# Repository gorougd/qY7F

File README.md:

### MPU based on STM32MP157

* Hardware design: 100Mbps Ethernet (TO BE FIXED)
* 512MB / 4Gbit DDR3L single bank (routed on PCB)
* 40pin RGB Screen adapter
* No PMU, discrete DC-DC power

By Gorougd, ZxS at Spring / Early Summer 2024

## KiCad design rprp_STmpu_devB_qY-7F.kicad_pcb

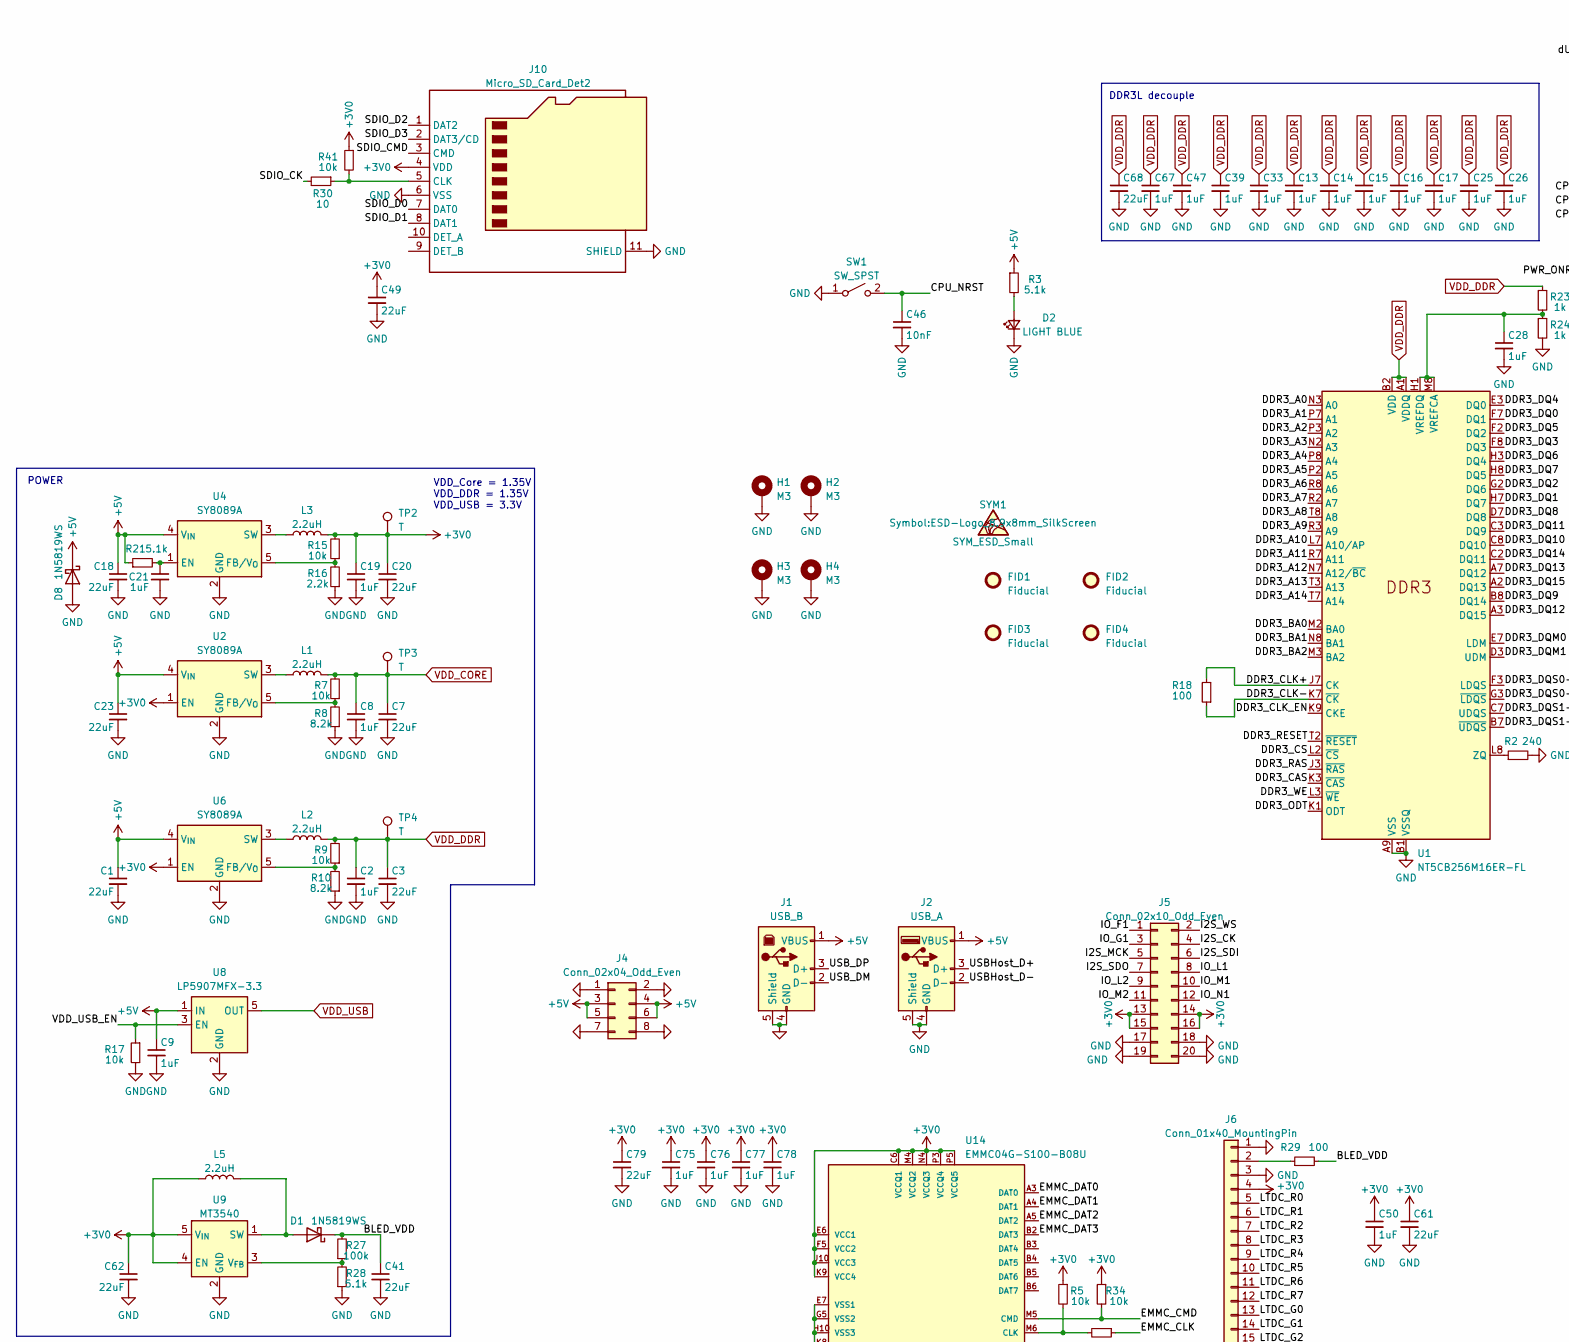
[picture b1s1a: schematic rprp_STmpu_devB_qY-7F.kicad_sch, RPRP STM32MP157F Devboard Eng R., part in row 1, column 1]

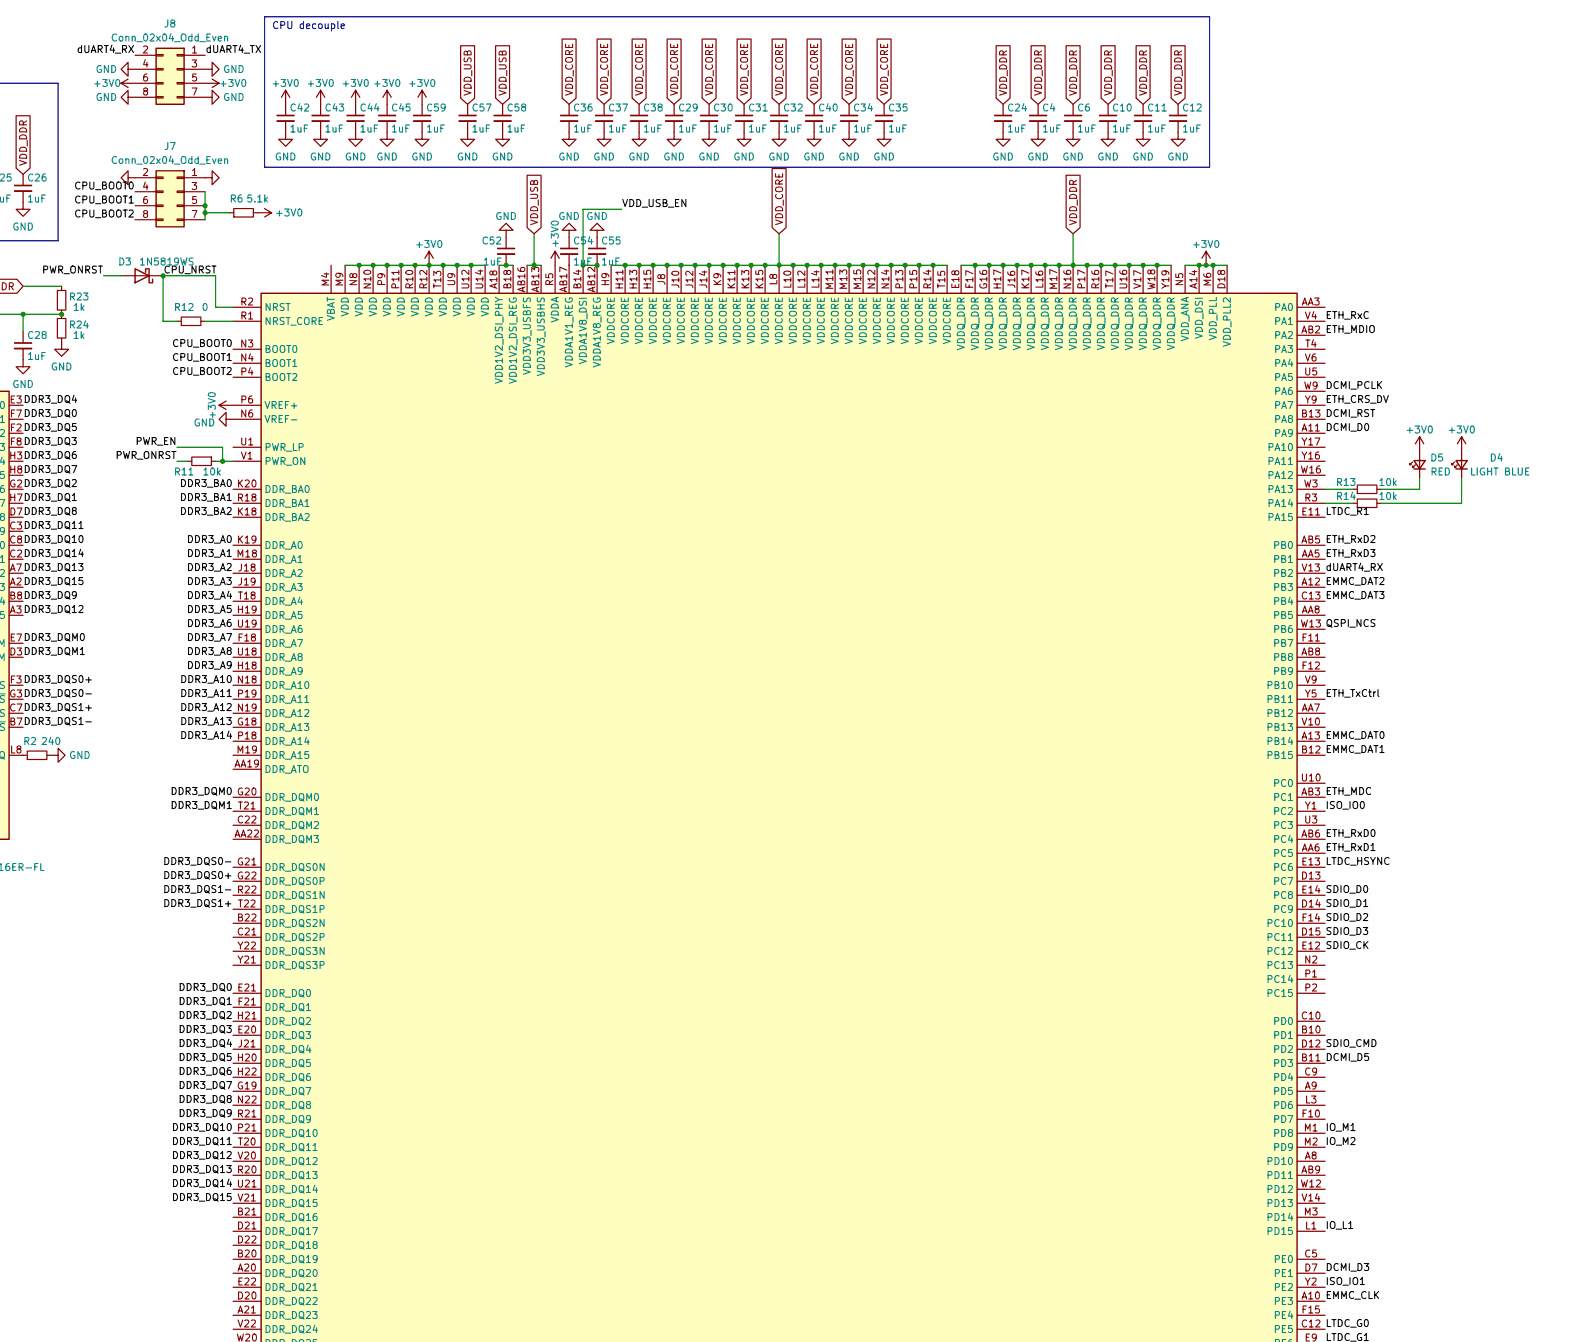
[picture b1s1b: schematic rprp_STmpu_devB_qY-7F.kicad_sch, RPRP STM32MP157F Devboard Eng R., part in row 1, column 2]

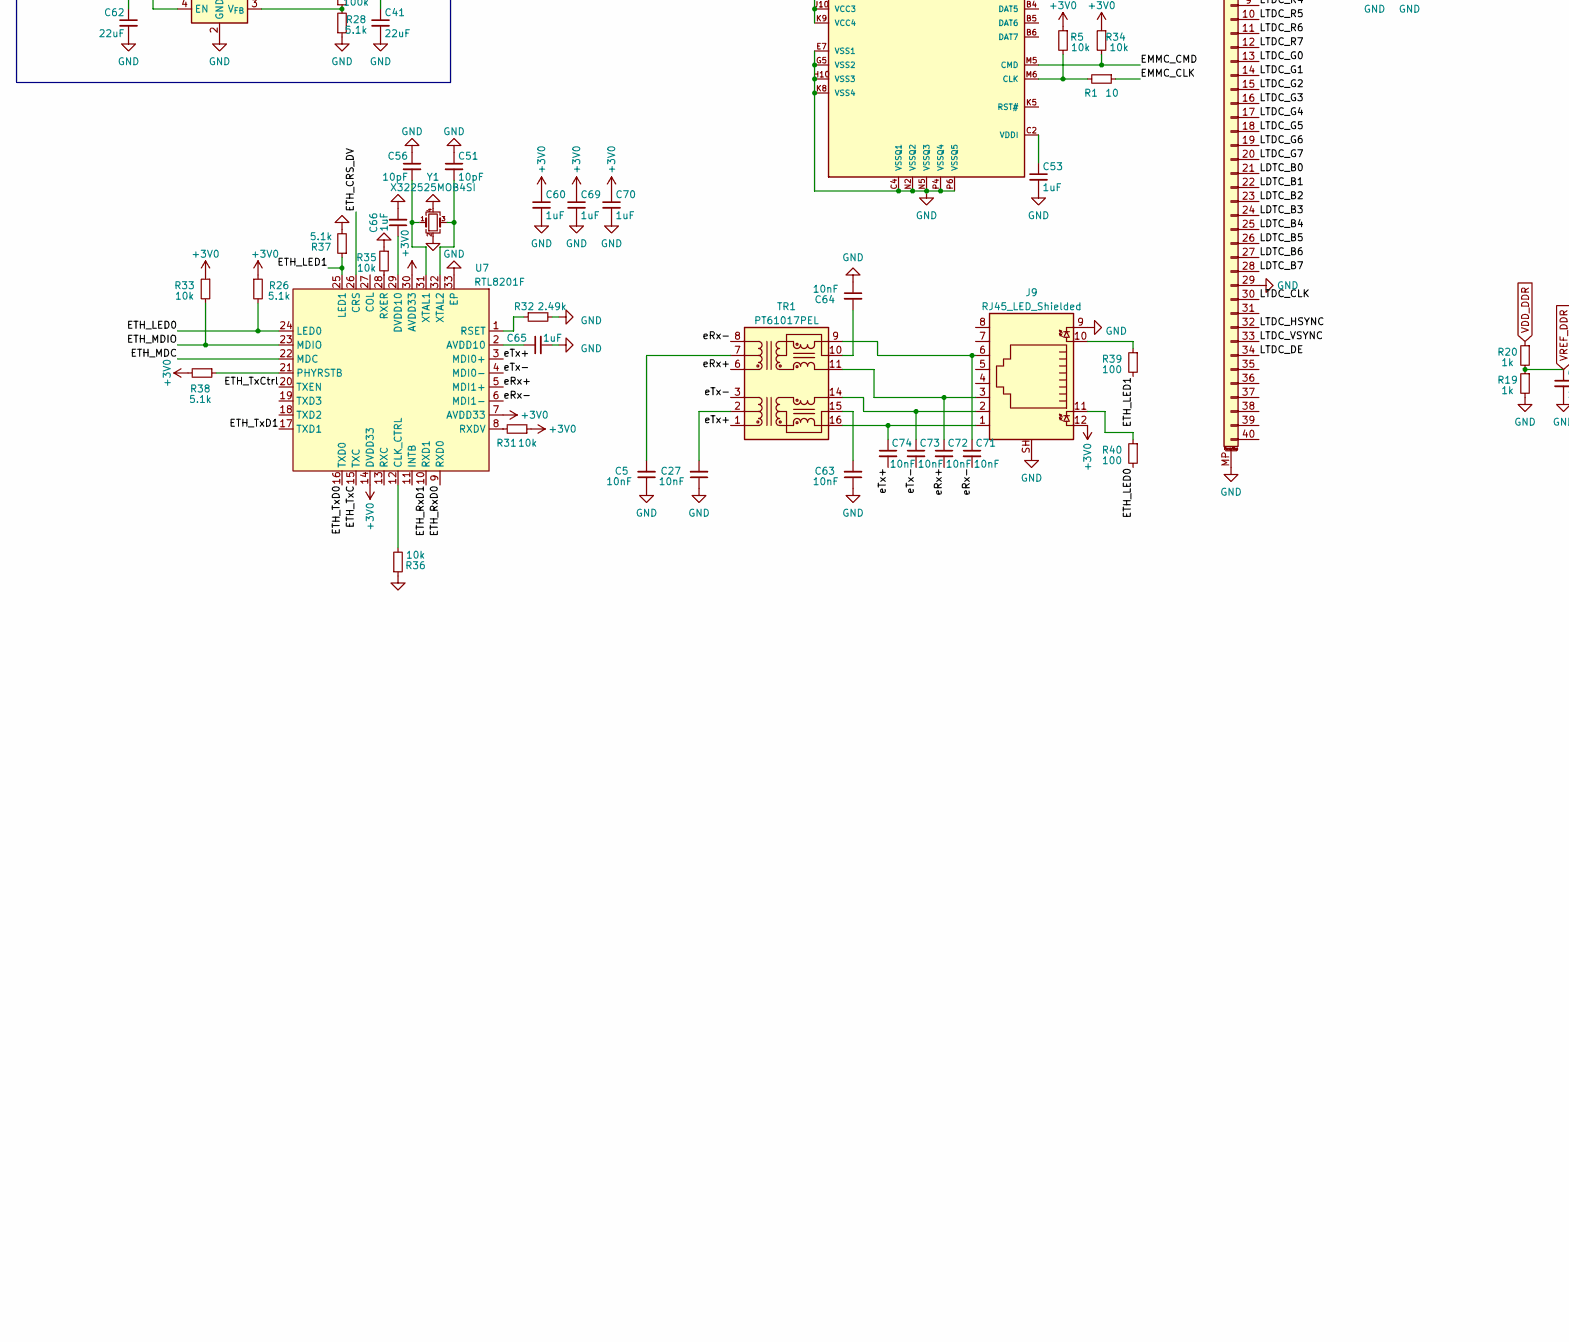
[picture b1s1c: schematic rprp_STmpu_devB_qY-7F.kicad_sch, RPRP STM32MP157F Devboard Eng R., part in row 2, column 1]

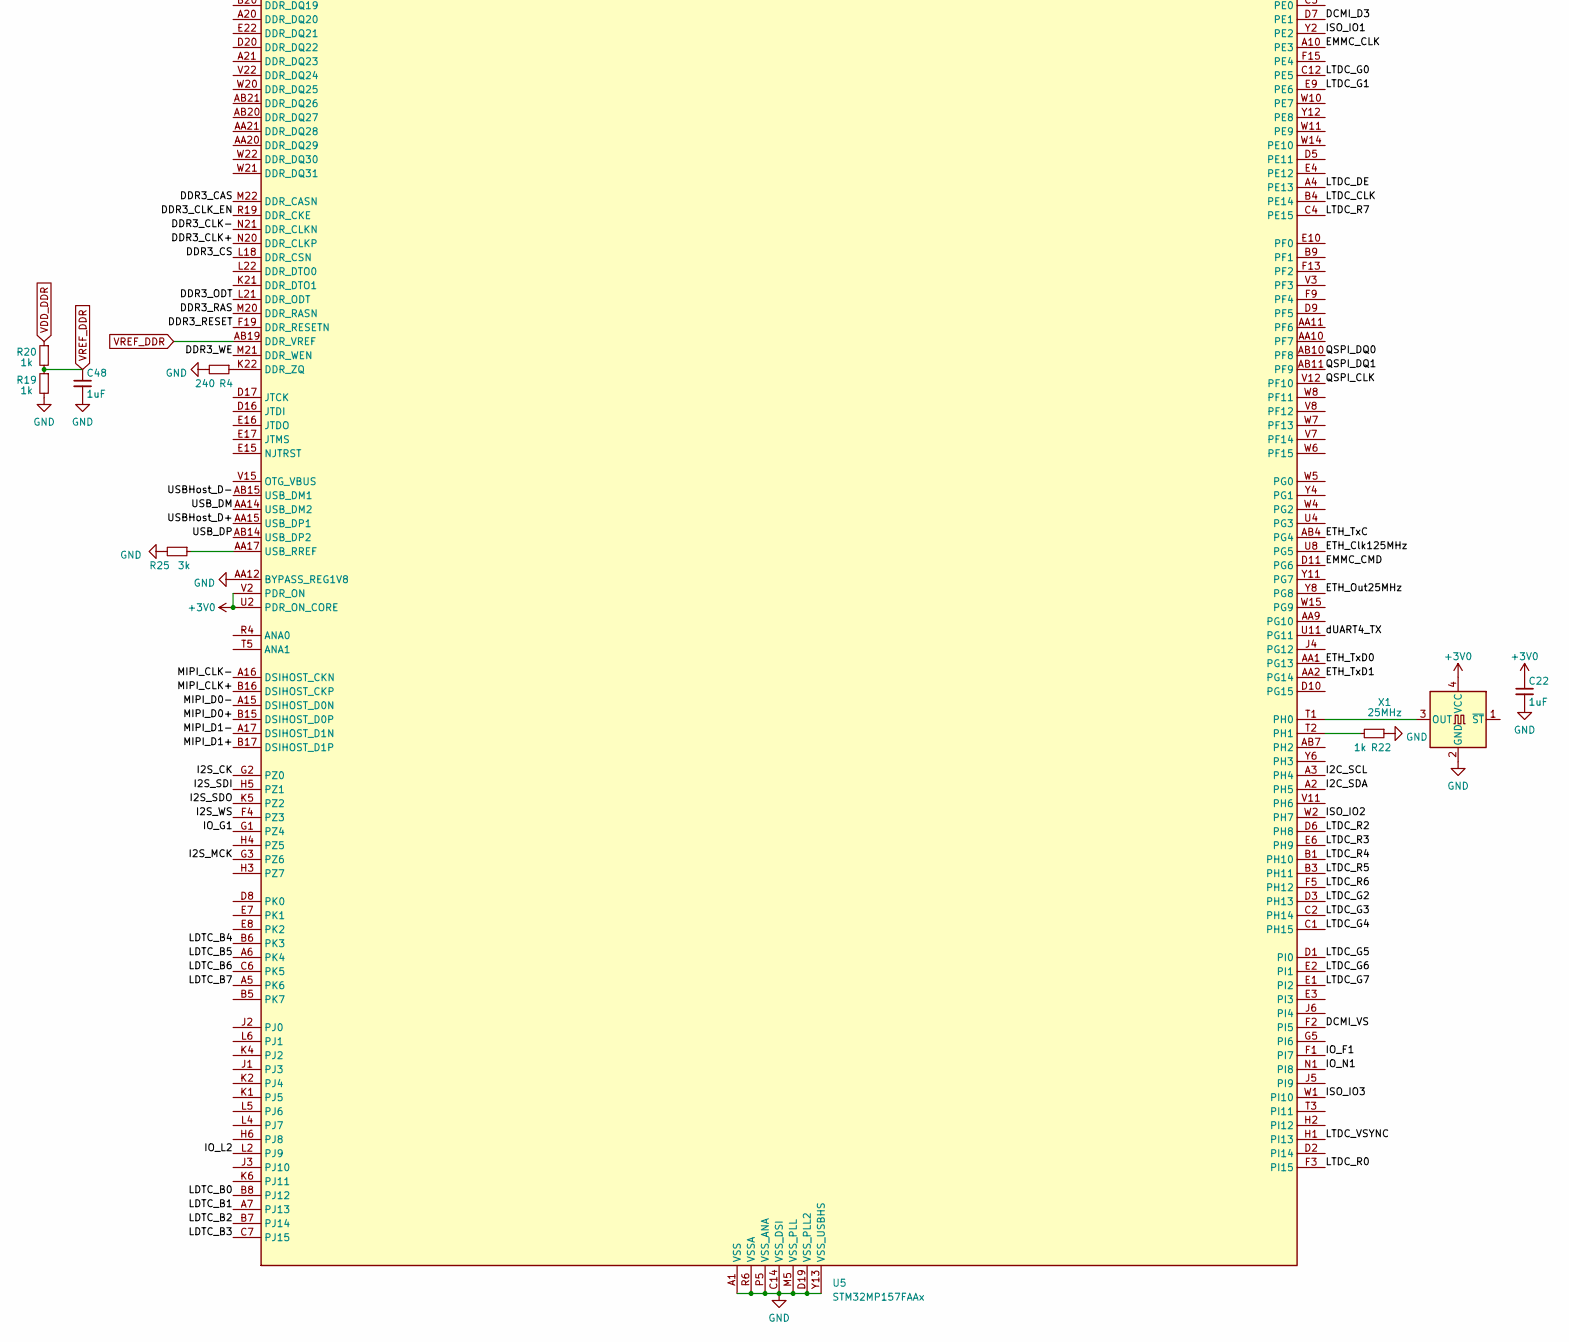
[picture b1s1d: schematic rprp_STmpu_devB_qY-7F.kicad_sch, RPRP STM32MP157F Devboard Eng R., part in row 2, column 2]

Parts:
C1, C3, C7, C18, C20, C23, C41, C49, C61, C62, C68, C79: 22uF; C_0805_2012Metric
C2, C8, C9, C19: 1uF; C_0603_1608Metric
C4, C6, C10, C11, C12, C13, C14, C15, C16, C17, C21, C22, C24, C25, C26, C28, C29, C30, C31, C32, C33, C34, C35, C36, C37, C38, C39, C40, C42, C43, C44, C45, C47, C48, C50, C52, C53, C54, C55, C57, C58, C59, C60, C65, C66, C67, C69, C70, C75, C76, C77, C78: 1uF; C_0402_1005Metric
C5, C27, C46, C63, C64, C71, C72, C73, C74: 10nF; C_0402_1005Metric
C51, C56: 10pF; C_0402_1005Metric
D1, D3, D8: 1N5819WS; D_SOD-323
D2, D4: LIGHT BLUE; LED_0603_1608Metric
D5: RED; LED_0603_1608Metric
FID1, FID2, FID3, FID4: Fiducial; Fiducial_0.5mm_Mask1.5mm
H1, H2, H3, H4: M3; MountingHole_3.2mm_M3_Pad_Via
J1: USB_B; USB_B_OST_USB-B1HSxx_Horizontal
J2: USB_A; USB_A_CONNFLY_DS1095-WNR0
J4, J7, J8: Conn_02x04_Odd_Even; PinHeader_2x04_P2.54mm_Vertical
J5: Conn_02x10_Odd_Even; PinHeader_2x10_P2.54mm_Vertical
J6: Conn_01x40_MountingPin; Hirose_FH12-40S-0.5SH_1x40-1MP_P0.50mm_Horizontal
J9: RJ45_LED_Shielded; RJ45_Amphenol_RJHSE538X
J10: Micro_SD_Card_Det2; Yu-MicroSD-TF-01A
L1, L2, L3, L5: 2.2uH; L_1008_2520Metric
R1, R30: 10; R_0402_1005Metric
R2, R4: 240; R_0402_1005Metric
R3, R6, R21, R28: 5.1k; R_0603_1608Metric
R5, R11, R17, R31, R33, R34, R35, R36, R41: 10k; R_0402_1005Metric
R7, R9, R13, R14, R15: 10k; R_0603_1608Metric
R8, R10: 8.2k; R_0603_1608Metric
R12: 0; R_0402_1005Metric
R16: 2.2k; R_0603_1608Metric
R18, R39, R40: 100; R_0402_1005Metric
R19, R20, R22, R23, R24: 1k; R_0402_1005Metric
R25: 3k; R_0402_1005Metric
R26, R37, R38: 5.1k; R_0402_1005Metric
R27: 100k; R_0603_1608Metric
R29: 100; R_0603_1608Metric
R32: 2.49k; R_0402_1005Metric
SW1: SW_SPST; SW_Push_1P1T_XKB_TS-1187A
SYM1: SYM_ESD_Small; ESD-Logo_8.9x8mm_SilkScreen
TP2, TP3, TP4: T; TestPoint_Pad_D1.0mm
TR1: PT61017PEL; Transformer_Ethernet_Bourns_PT61017PEL
U1: NT5CB256M16ER-FL; BGA-96_9.0x13.0mm_Layout2x3x16_P0.8mm
U2, U4, U6: SY8089A; TSOT-23-5
U5: STM32MP157FAAx; ST_LFBGA-448_18x18mm_Layout22x22_P0.8mm
U7: RTL8201F; QFN-32-1EP_5x5mm_P0.5mm_EP3.65x3.65mm
U8: LP5907MFX-3.3; SOT-23-5
U9: MT3540; SOT-23-5
U14: EMMC04G-S100-B08U; MICRON_EMMC_153
X1: 25MHz; Crystal_SMD_EuroQuartz_MT-4Pin_3.2x2.5mm
Y1: X322525MOB4SI; Crystal_SMD_EuroQuartz_MT-4Pin_3.2x2.5mm

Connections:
+3V0: C19.1, C20.1, C22.1, C42.1, C43.1, C44.1, C45.1, C49.1, C50.1, C59.1, C60.1, C61.1, C62.1, C69.1, C70.1, C75.1, C76.1, C77.1, C78.1, C79.1, D4.2 (A), D5.2 (A), J5.13, J5.14, J5.15, J5.16, J6.4, J8.5, J8.6, J9.12, J10.4 (VDD), L3.2, L5.1, R5.1, R6.2, R15.2, R26.1, R31.1, R33.1, R34.1, R38.2, R41.1, TP2.1, U2.1 (EN), U5.A14 (VDD_DSI), U5.D18 (VDD_PLL2), U5.M6 (VDD_PLL), U5.M9 (VDD), U5.N5 (VDD_ANA), U5.N8 (VDD), U5.N10 (VDD), U5.P6 (VREF+), U5.P9 (VDD), U5.P11 (VDD), U5.R5 (VDDA), U5.R10 (VDD), U5.R12 (VDD), U5.T13 (VDD), U5.U2 (PDR_ON_CORE), U5.U9 (VDD), U5.U12 (VDD), U5.U14 (VDD), U5.V2 (PDR_ON), U6.1 (EN), U7.7 (AVDD33), U7.14 (DVDD33), U7.30 (AVDD33), U9.4 (EN), U9.5 (V_{IN}), U14.C6 (VCCQ1), U14.E6 (VCC1), U14.F5 (VCC2), U14.J10 (VCC3), U14.K9 (VCC4), U14.M4 (VCCQ2), U14.N4 (VCCQ3), U14.P3 (VCCQ4), U14.P5 (VCCQ5), X1.4 (VCC)
+5V: C1.1, C9.1, C18.1, C23.1, D8.1 (K), J1.1 (VBUS), J2.1 (VBUS), J4.3, J4.4, J4.5, J4.6, R3.1, R21.1, U2.4 (V_{IN}), U4.4 (V_{IN}), U6.4 (V_{IN}), U8.1 (IN)
/BLED_VDD: C41.1, D1.1 (K), R27.2, R29.2
/CPU_BOOT0: J7.4, U5.N3 (BOOT0)
/CPU_BOOT1: J7.6, U5.N4 (BOOT1)
/CPU_BOOT2: J7.8, U5.P4 (BOOT2)
/CPU_NRST: C46.1, D3.1 (K), R12.1, SW1.2 (B), U5.R2 (NRST)
/DCMI_D0: U5.A11 (PA9)
/DCMI_D3: U5.D7 (PE1)
/DCMI_D5: U5.B11 (PD3)
/DCMI_PCLK: U5.W9 (PA6)
/DCMI_RST: U5.B13 (PA8)
/DCMI_VS: U5.F2 (PI5)
/DDR3_A0: U1.N3 (A0), U5.K19 (DDR_A0)
/DDR3_A1: U1.P7 (A1), U5.M18 (DDR_A1)
/DDR3_A2: U1.P3 (A2), U5.J18 (DDR_A2)
/DDR3_A3: U1.N2 (A3), U5.J19 (DDR_A3)
/DDR3_A4: U1.P8 (A4), U5.T18 (DDR_A4)
/DDR3_A5: U1.P2 (A5), U5.H19 (DDR_A5)
/DDR3_A6: U1.R8 (A6), U5.U19 (DDR_A6)
/DDR3_A7: U1.R2 (A7), U5.F18 (DDR_A7)
/DDR3_A8: U1.T8 (A8), U5.U18 (DDR_A8)
/DDR3_A9: U1.R3 (A9), U5.H18 (DDR_A9)
/DDR3_A10: U1.L7 (A10/AP), U5.N18 (DDR_A10)
/DDR3_A11: U1.R7 (A11), U5.P19 (DDR_A11)
/DDR3_A12: U1.N7 (A12/~BC), U5.N19 (DDR_A12)
/DDR3_A13: U1.T3 (A13), U5.G18 (DDR_A13)
/DDR3_A14: U1.T7 (A14), U5.P18 (DDR_A14)
/DDR3_BA0: U1.M2 (BA0), U5.K20 (DDR_BA0)
/DDR3_BA1: U1.N8 (BA1), U5.R18 (DDR_BA1)
/DDR3_BA2: U1.M3 (BA2), U5.K18 (DDR_BA2)
/DDR3_CAS: U1.K3 (~CAS), U5.M22 (DDR_CASN)
/DDR3_CLK+: R18.2, U1.J7 (CK), U5.N20 (DDR_CLKP)
/DDR3_CLK-: R18.1, U1.K7 (~CK), U5.N21 (DDR_CLKN)
/DDR3_CLK_EN: U1.K9 (CKE), U5.R19 (DDR_CKE)
/DDR3_CS: U1.L2 (~CS), U5.L18 (DDR_CSN)
/DDR3_DQ0: U1.F7 (DQ1), U5.E21 (DDR_DQ0)
/DDR3_DQ1: U1.H7 (DQ7), U5.F21 (DDR_DQ1)
/DDR3_DQ2: U1.G2 (DQ6), U5.H21 (DDR_DQ2)
/DDR3_DQ3: U1.F8 (DQ3), U5.E20 (DDR_DQ3)
/DDR3_DQ4: U1.E3 (DQ0), U5.J21 (DDR_DQ4)
/DDR3_DQ5: U1.F2 (DQ2), U5.H20 (DDR_DQ5)
/DDR3_DQ6: U1.H3 (DQ4), U5.H22 (DDR_DQ6)
/DDR3_DQ7: U1.H8 (DQ5), U5.G19 (DDR_DQ7)
/DDR3_DQ8: U1.D7 (DQ8), U5.N22 (DDR_DQ8)
/DDR3_DQ9: U1.B8 (DQ14), U5.R21 (DDR_DQ9)
/DDR3_DQ10: U1.C8 (DQ10), U5.P21 (DDR_DQ10)
/DDR3_DQ11: U1.C3 (DQ9), U5.T20 (DDR_DQ11)
/DDR3_DQ12: U1.A3 (DQ15), U5.V20 (DDR_DQ12)
/DDR3_DQ13: U1.A7 (DQ12), U5.R20 (DDR_DQ13)
/DDR3_DQ14: U1.C2 (DQ11), U5.U21 (DDR_DQ14)
/DDR3_DQ15: U1.A2 (DQ13), U5.V21 (DDR_DQ15)
/DDR3_DQM0: U1.E7 (LDM), U5.G20 (DDR_DQM0)
/DDR3_DQM1: U1.D3 (UDM), U5.T21 (DDR_DQM1)
/DDR3_DQS0+: U1.F3 (LDQS), U5.G22 (DDR_DQS0P)
/DDR3_DQS0-: U1.G3 (~LDQS), U5.G21 (DDR_DQS0N)
/DDR3_DQS1+: U1.C7 (UDQS), U5.T22 (DDR_DQS1P)
/DDR3_DQS1-: U1.B7 (~UDQS), U5.R22 (DDR_DQS1N)
/DDR3_ODT: U1.K1 (ODT), U5.L21 (DDR_ODT)
/DDR3_RAS: U1.J3 (~RAS), U5.M20 (DDR_RASN)
/DDR3_RESET: U1.T2 (~RESET), U5.F19 (DDR_RESETN)
/DDR3_WE: U1.L3 (~WE), U5.M21 (DDR_WEN)
/EMMC_CLK: R1.1, U5.A10 (PE3)
/EMMC_CMD: R34.2, U5.D11 (PG6), U14.M5 (CMD)
/EMMC_DAT0: U5.A13 (PB14), U14.A3 (DAT0)
/EMMC_DAT1: U5.B12 (PB15), U14.A4 (DAT1)
/EMMC_DAT2: U5.A12 (PB3), U14.A5 (DAT2)
/EMMC_DAT3: U5.C13 (PB4), U14.B2 (DAT3)
/ETH_CRS_DV: U5.Y9 (PA7), U7.26 (CRS)
/ETH_Clk125MHz: U5.U8 (PG5)
/ETH_LED0: R26.2, R40.2, U7.24 (LED0)
/ETH_LED1: R37.1, R39.2, U7.25 (LED1)
/ETH_MDC: U5.AB3 (PC1), U7.22 (MDC)
/ETH_MDIO: R33.2, U5.AB2 (PA2), U7.23 (MDIO)
/ETH_Out25MHz: U5.Y8 (PG8)
/ETH_RxC: U5.V4 (PA1)
/ETH_RxD0: U5.AB6 (PC4), U7.9 (RXD0)
/ETH_RxD1: U5.AA6 (PC5), U7.10 (RXD1)
/ETH_RxD2: U5.AB5 (PB0)
/ETH_RxD3: U5.AA5 (PB1)
/ETH_TxC: U5.AB4 (PG4), U7.15 (TXC)
/ETH_TxCtrl: U5.Y5 (PB11), U7.20 (TXEN)
/ETH_TxD0: U5.AA1 (PG13), U7.16 (TXD0)
/ETH_TxD1: U5.AA2 (PG14), U7.17 (TXD1)
/I2C_SCL: U5.A3 (PH4)
/I2C_SDA: U5.A2 (PH5)
/I2S_CK: J5.4, U5.G2 (PZ0)
/I2S_MCK: J5.5, U5.G3 (PZ6)
/I2S_SDI: J5.6, U5.H5 (PZ1)
/I2S_SDO: J5.7, U5.K5 (PZ2)
/I2S_WS: J5.2, U5.F4 (PZ3)
/IO_F1: J5.1, U5.F1 (PI7)
/IO_G1: J5.3, U5.G1 (PZ4)
/IO_L1: J5.8, U5.L1 (PD15)
/IO_L2: J5.9, U5.L2 (PJ9)
/IO_M1: J5.10, U5.M1 (PD8)
/IO_M2: J5.11, U5.M2 (PD9)
/IO_N1: J5.12, U5.N1 (PI8)
/ISO_IO0: U5.Y1 (PC2)
/ISO_IO1: U5.Y2 (PE2)
/ISO_IO2: U5.W2 (PH7)
/ISO_IO3: U5.W1 (PI10)
/LDTC_B0: J6.21, U5.B8 (PJ12)
/LDTC_B1: J6.22, U5.A7 (PJ13)
/LDTC_B2: J6.23, U5.B7 (PJ14)
/LDTC_B3: J6.24, U5.C7 (PJ15)
/LDTC_B4: J6.25, U5.B6 (PK3)
/LDTC_B5: J6.26, U5.A6 (PK4)
/LDTC_B6: J6.27, U5.C6 (PK5)
/LDTC_B7: J6.28, U5.A5 (PK6)
/LTDC_CLK: J6.30, U5.B4 (PE14)
/LTDC_DE: J6.34, U5.A4 (PE13)
/LTDC_G0: J6.13, U5.C12 (PE5)
/LTDC_G1: J6.14, U5.E9 (PE6)
/LTDC_G2: J6.15, U5.D3 (PH13)
/LTDC_G3: J6.16, U5.C2 (PH14)
/LTDC_G4: J6.17, U5.C1 (PH15)
/LTDC_G5: J6.18, U5.D1 (PI0)
/LTDC_G6: J6.19, U5.E2 (PI1)
/LTDC_G7: J6.20, U5.E1 (PI2)
/LTDC_HSYNC: J6.32, U5.E13 (PC6)
/LTDC_R0: J6.5, U5.F3 (PI15)
/LTDC_R1: J6.6, U5.E11 (PA15)
/LTDC_R2: J6.7, U5.D6 (PH8)
/LTDC_R3: J6.8, U5.E6 (PH9)
/LTDC_R4: J6.9, U5.B1 (PH10)
/LTDC_R5: J6.10, U5.B3 (PH11)
/LTDC_R6: J6.11, U5.F5 (PH12)
/LTDC_R7: J6.12, U5.C4 (PE15)
/LTDC_VSYNC: J6.33, U5.H1 (PI13)
/MIPI_CLK+: U5.B16 (DSIHOST_CKP)
/MIPI_CLK-: U5.A16 (DSIHOST_CKN)
/MIPI_D0+: U5.B15 (DSIHOST_D0P)
/MIPI_D0-: U5.A15 (DSIHOST_D0N)
/MIPI_D1+: U5.B17 (DSIHOST_D1P)
/MIPI_D1-: U5.A17 (DSIHOST_D1N)
/PWR_EN: R11.1, U5.V1 (PWR_ON)
/PWR_ONRST: D3.2 (A), R11.2
/QSPI_CLK: U5.V12 (PF10)
/QSPI_DQ0: U5.AB10 (PF8)
/QSPI_DQ1: U5.AB11 (PF9)
/QSPI_NCS: U5.W13 (PB6)
/SDIO_CK: R30.2, U5.E12 (PC12)
/SDIO_CMD: J10.3 (CMD), U5.D12 (PD2)
/SDIO_D0: J10.7 (DAT0), U5.E14 (PC8)
/SDIO_D1: J10.8 (DAT1), U5.D14 (PC9)
/SDIO_D2: J10.1 (DAT2), U5.F14 (PC10)
/SDIO_D3: J10.2 (DAT3/CD), U5.D15 (PC11)
/USBHost_D+: J2.3 (D+), U5.AA15 (USB_DP1)
/USBHost_D-: J2.2 (D-), U5.AB15 (USB_DM1)
/USB_DM: J1.2 (D-), U5.AA14 (USB_DM2)
/USB_DP: J1.3 (D+), U5.AB14 (USB_DP2)
/VDD_USB_EN: C55.2, R17.1, U5.AB12 (VDDA1V8_REG), U5.B14 (VDDA1V8_DSI), U8.3 (EN)
/dUART4_RX: J8.2, U5.V13 (PB2)
/dUART4_TX: J8.1, U5.U11 (PG11)
/eRx+: C72.2, TR1.6 (RD+), U7.5 (MDI1+)
/eRx-: C71.2, TR1.8 (RD-), U7.6 (MDI1-)
/eTx+: C74.2, TR1.1 (TD+), U7.3 (MDI0+)
/eTx-: C73.2, TR1.3 (TD-), U7.4 (MDI0-)
GND: C1.2, C2.2, C3.2, C4.2, C5.1, C6.2, C7.2, C8.2, C9.2, C10.2, C11.2, C12.2, C13.2, C14.2, C15.2, C16.2, C17.2, C18.2, C19.2, C20.2, C21.2, C22.2, C23.2, C24.2, C25.2, C26.2, C27.1, C28.2, C29.2, C30.2, C31.2, C32.2, C33.2, C34.2, C35.2, C36.2, C37.2, C38.2, C39.2, C40.2, C41.2, C42.2, C43.2, C44.2, C45.2, C46.2, C47.2, C48.2, C49.2, C50.2, C51.1, C52.1, C53.2, C54.1, C55.1, C56.1, C57.2, C58.2, C59.2, C60.2, C61.2, C62.2, C63.1, C64.1, C65.2, C66.2, C67.2, C68.2, C69.2, C70.2, C75.2, C76.2, C77.2, C78.2, C79.2, D2.1 (K), D8.2 (A), H1.1, H2.1, H3.1, H4.1, J1.4 (GND), J1.5 (Shield), J2.4 (GND), J2.5 (Shield), J4.1, J4.2, J4.7, J4.8, J5.17, J5.18, J5.19, J5.20, J6.1, J6.3, J6.29, J6.MP (MountPin), J7.1, J7.2, J8.3, J8.4, J8.7, J8.8, J9.9, J9.SH, J10.6 (VSS), J10.11 (SHIELD), R2.2, R4.2, R8.1, R10.1, R16.1, R17.2, R19.2, R22.1, R24.2, R25.2, R28.1, R32.2, R35.1, R36.1, R37.2, SW1.1 (A), U1.A9 (VSS), U1.B1 (VSSQ), U1.B3 (VSS), U1.B9 (VSSQ), U1.D1 (VSSQ), U1.D8 (VSSQ), U1.E1 (VSS), U1.E2 (VSSQ), U1.E8 (VSSQ), U1.F9 (VSSQ), U1.G1 (VSSQ), U1.G8 (VSS), U1.G9 (VSSQ), U1.J2 (VSS), U1.J8 (VSS), U1.M1 (VSS), U1.M9 (VSS), U1.P1 (VSS), U1.P9 (VSS), U1.T1 (VSS), U1.T9 (VSS), U2.2 (GND), U4.2 (GND), U5.A1 (VSS), U5.A19 (VSS), U5.A22 (VSS), U5.AA4 (VSS), U5.AA12 (BYPASS_REG1V8), U5.AA13 (VSS_USBHS), U5.AA16 (VSS_USBHS), U5.AA18 (VSS), U5.AB1 (VSS), U5.AB18 (VSS), U5.AB22 (VSS), U5.B2 (VSS), U5.B19 (VSS), U5.C3 (VSS), U5.C8 (VSS), U5.C11 (VSS), U5.C14 (VSS_DSI), U5.C15 (VSS_DSI), U5.C16 (VSS_DSI), U5.C17 (VSS_DSI), U5.C18 (VSS_DSI), U5.C19 (VSS), U5.C20 (VSS), U5.D4 (VSS), U5.D19 (VSS_PLL2), U5.E5 (VSS), U5.E19 (VSS), U5.F6 (VSS), U5.F7 (VSS), U5.F8 (VSS), U5.F16 (VSS), U5.F20 (VSS), U5.G4 (VSS), U5.G6 (VSS), U5.G8 (VSS), U5.G10 (VSS), U5.G12 (VSS), U5.G14 (VSS), U5.G17 (VSS), U5.H7 (VSS), U5.J9 (VSS), U5.J11 (VSS), U5.J13 (VSS), U5.J17 (VSS), U5.J20 (VSS), U5.K3 (VSS), U5.K7 (VSS), U5.K10 (VSS), U5.K12 (VSS), U5.K14 (VSS), U5.L9 (VSS), U5.L11 (VSS), U5.L13 (VSS), U5.L17 (VSS), U5.L19 (VSS), U5.L20 (VSS), U5.M5 (VSS_PLL), U5.M7 (VSS), U5.M10 (VSS), U5.M12 (VSS), U5.M14 (VSS), U5.N6 (VREF-), U5.N9 (VSS), U5.N11 (VSS), U5.N13 (VSS), U5.N17 (VSS), U5.P3 (VSS), U5.P5 (VSS_ANA), U5.P7 (VSS), U5.P10 (VSS), U5.P12 (VSS), U5.P14 (VSS), U5.P20 (VSS), U5.R6 (VSSA), U5.R8 (VSS), U5.R17 (VSS), U5.T6 (VSSA), U5.T7 (VSS), U5.T9 (VSS), U5.T11 (VSS), U5.T19 (VSS), U5.U6 (VSSA), U5.U7 (VSS), U5.U13 (VSS), U5.U15 (VSS), U5.U17 (VSS), U5.U20 (VSS), U5.V5 (VSS), U5.V16 (VSS), U5.V18 (VSS), U5.V19 (VSS), U5.W17 (VSS), U5.W19 (VSS), U5.Y3 (VSS), U5.Y7 (VSS), U5.Y10 (VSS), U5.Y13 (VSS_USBHS), U5.Y14 (VSS_USBHS), U5.Y15 (VSS_USBHS), U5.Y18 (VSS), U5.Y20 (VSS), U6.2 (GND), U7.33 (EP), U8.2 (GND), U9.2 (GND), U14.C4 (VSSQ1), U14.E7 (VSS1), U14.G5 (VSS2), U14.H10 (VSS3), U14.K8 (VSS4), U14.N2 (VSSQ2), U14.N5 (VSSQ3), U14.P4 (VSSQ4), U14.P6 (VSSQ5), X1.2 (GND), Y1.2, Y1.4
unnamed: D1.2 (A), L5.2, U9.1 (SW)
unnamed: D2.2 (A), R3.2
unnamed: D4.1 (K), R14.2
unnamed: D5.1 (K), R13.2
unnamed: J6.2, R29.1
unnamed: J7.3, J7.5, J7.7, R6.1
unnamed: J9.10, R39.1
unnamed: J9.11, R40.1
unnamed: J10.5 (CLK), R30.1, R41.2
unnamed: C5.2, TR1.7 (C_RD)
unnamed: C64.2, TR1.10 (C_RX)
unnamed: C27.2, TR1.2 (C_TD)
unnamed: C63.2, TR1.15 (C_TX)
unnamed: C72.1, J9.3, TR1.11 (RX+)
unnamed: C71.1, J9.6, TR1.9 (RX-)
unnamed: C74.1, J9.1, TR1.16 (TX+)
unnamed: C73.1, J9.2, TR1.14 (TX-)
unnamed: C28.1, R23.2, R24.1, U1.H1 (VREFDQ), U1.M8 (VREFCA)
unnamed: R2.1, U1.L8 (ZQ)
unnamed: R7.1, R8.2, U2.5 (FB/V_{O})
unnamed: L1.1, U2.3 (SW)
unnamed: C21.1, R21.2, U4.1 (EN)
unnamed: R15.1, R16.2, U4.5 (FB/V_{O})
unnamed: L3.1, U4.3 (SW)
unnamed: R4.1, U5.K22 (DDR_ZQ)
unnamed: R12.2, U5.R1 (NRST_CORE)
unnamed: R13.1, U5.W3 (PA13)
unnamed: R14.1, U5.R3 (PA14)
unnamed: U5.T1 (PH0), X1.3 (OUT)
unnamed: R22.2, U5.T2 (PH1)
unnamed: R25.1, U5.AA17 (USB_RREF)
unnamed: C52.2, U5.A18 (VDD1V2_DSI_PHY), U5.B18 (VDD1V2_DSI_REG)
unnamed: C54.2, U5.AB17 (VDDA1V1_REG)
unnamed: R9.1, R10.2, U6.5 (FB/V_{O})
unnamed: L2.1, U6.3 (SW)
unnamed: C65.1, U7.2 (AVDD10)
unnamed: R36.2, U7.12 (CLK_CTRL)
unnamed: C66.1, U7.29 (DVDD10)
unnamed: R38.1, U7.21 (PHYRSTB)
unnamed: R32.1, U7.1 (RSET)
unnamed: R31.2, U7.8 (RXDV)
unnamed: R35.2, U7.28 (RXER)
unnamed: C56.2, U7.31 (XTAL1), Y1.1
unnamed: C51.2, U7.32 (XTAL2), Y1.3
unnamed: R27.1, R28.2, U9.3 (V_{FB})
unnamed: R1.2, R5.2, U14.M6 (CLK)
unnamed: C53.1, U14.C2 (VDDI)
VDD_CORE: C7.1, C8.1, C29.1, C30.1, C31.1, C32.1, C34.1, C35.1, C36.1, C37.1, C38.1, C40.1, L1.2, R7.2, TP3.1, U5.H9 (VDDCORE), U5.H11 (VDDCORE), U5.H13 (VDDCORE), U5.H15 (VDDCORE), U5.J8 (VDDCORE), U5.J10 (VDDCORE), U5.J12 (VDDCORE), U5.J14 (VDDCORE), U5.K9 (VDDCORE), U5.K11 (VDDCORE), U5.K13 (VDDCORE), U5.K15 (VDDCORE), U5.L8 (VDDCORE), U5.L10 (VDDCORE), U5.L12 (VDDCORE), U5.L14 (VDDCORE), U5.M11 (VDDCORE), U5.M13 (VDDCORE), U5.M15 (VDDCORE), U5.N12 (VDDCORE), U5.N14 (VDDCORE), U5.P13 (VDDCORE), U5.P15 (VDDCORE), U5.R14 (VDDCORE), U5.T15 (VDDCORE)
VDD_DDR: C2.1, C3.1, C4.1, C6.1, C10.1, C11.1, C12.1, C13.1, C14.1, C15.1, C16.1, C17.1, C24.1, C25.1, C26.1, C33.1, C39.1, C47.1, C67.1, C68.1, L2.2, R9.2, R20.1, R23.1, TP4.1, U1.A1 (VDDQ), U1.A8 (VDDQ), U1.B2 (VDD), U1.C1 (VDDQ), U1.C9 (VDDQ), U1.D2 (VDDQ), U1.D9 (VDD), U1.E9 (VDDQ), U1.F1 (VDDQ), U1.G7 (VDD), U1.H2 (VDDQ), U1.H9 (VDDQ), U1.K2 (VDD), U1.K8 (VDD), U1.N1 (VDD), U1.N9 (VDD), U1.R1 (VDD), U1.R9 (VDD), U5.E18 (VDDQ_DDR), U5.F17 (VDDQ_DDR), U5.G16 (VDDQ_DDR), U5.H17 (VDDQ_DDR), U5.J16 (VDDQ_DDR), U5.K17 (VDDQ_DDR), U5.L16 (VDDQ_DDR), U5.M17 (VDDQ_DDR), U5.N16 (VDDQ_DDR), U5.P17 (VDDQ_DDR), U5.R16 (VDDQ_DDR), U5.T17 (VDDQ_DDR), U5.U16 (VDDQ_DDR), U5.V17 (VDDQ_DDR), U5.W18 (VDDQ_DDR), U5.Y19 (VDDQ_DDR)
VDD_USB: C57.1, C58.1, U5.AB13 (VDD3V3_USBHS), U5.AB16 (VDD3V3_USBFS), U8.5 (OUT)
VREF_DDR: C48.1, R19.1, R20.2, U5.AB19 (DDR_VREF)

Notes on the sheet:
VDD_Core = 1.35V VDD_DDR = 1.35V VDD_USB = 3.3V
POWER
DDR3L decouple
CPU decouple

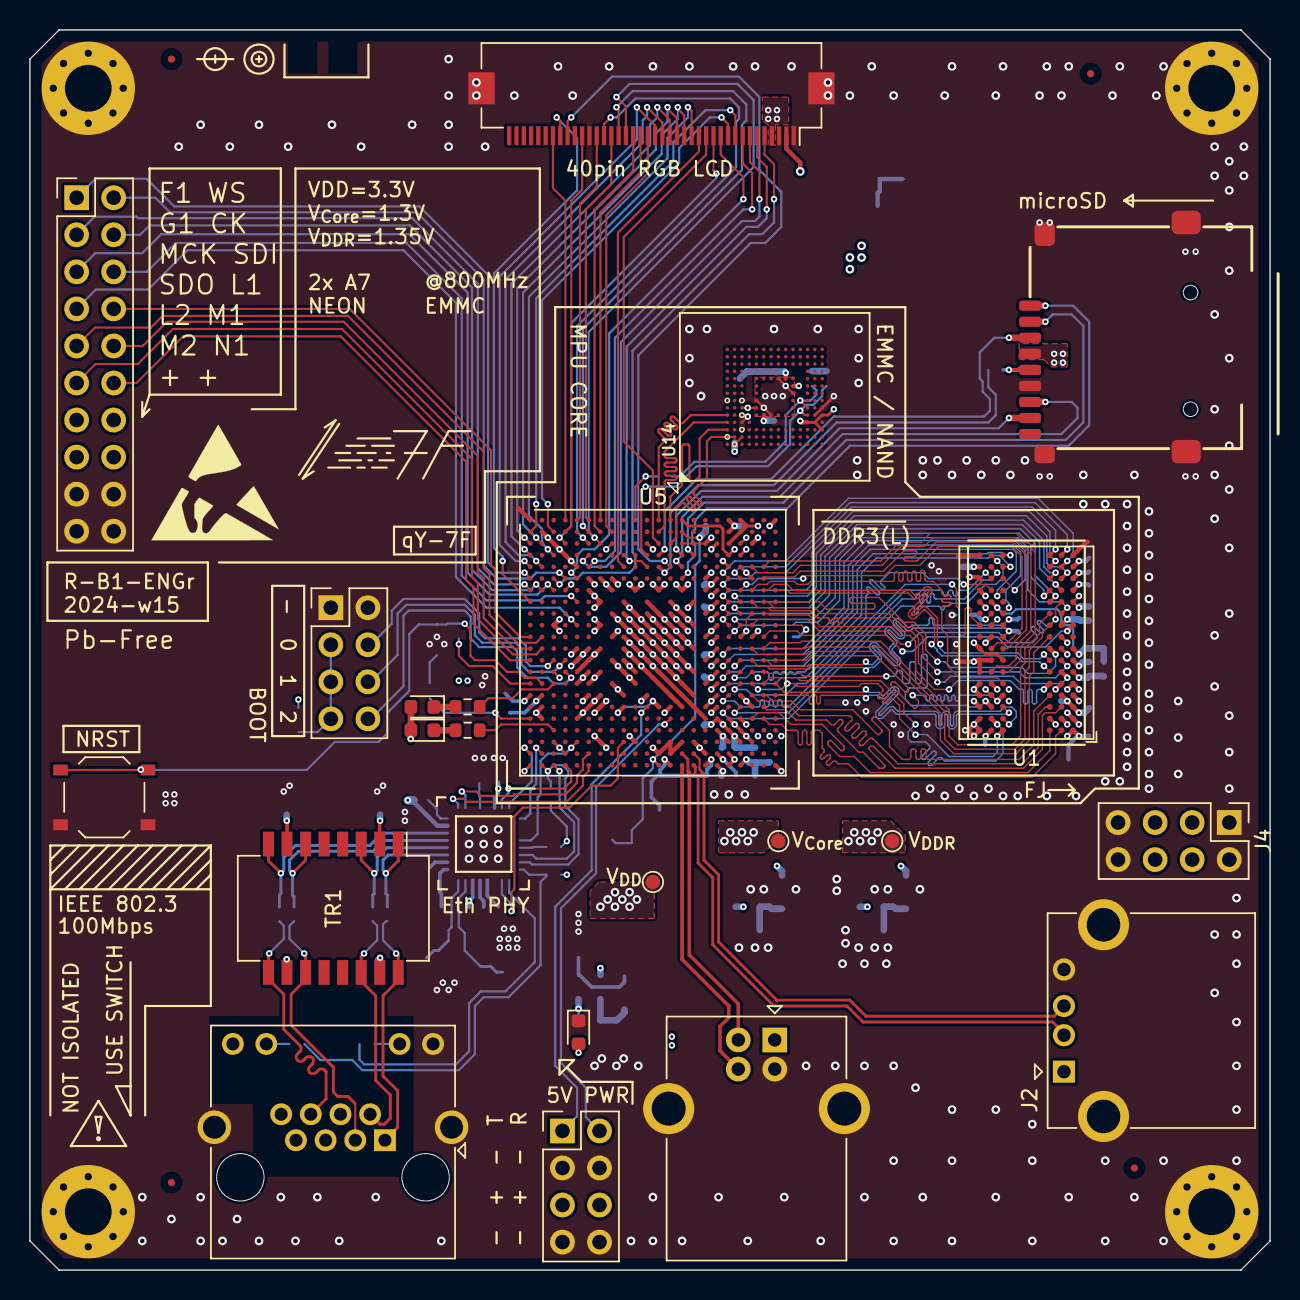
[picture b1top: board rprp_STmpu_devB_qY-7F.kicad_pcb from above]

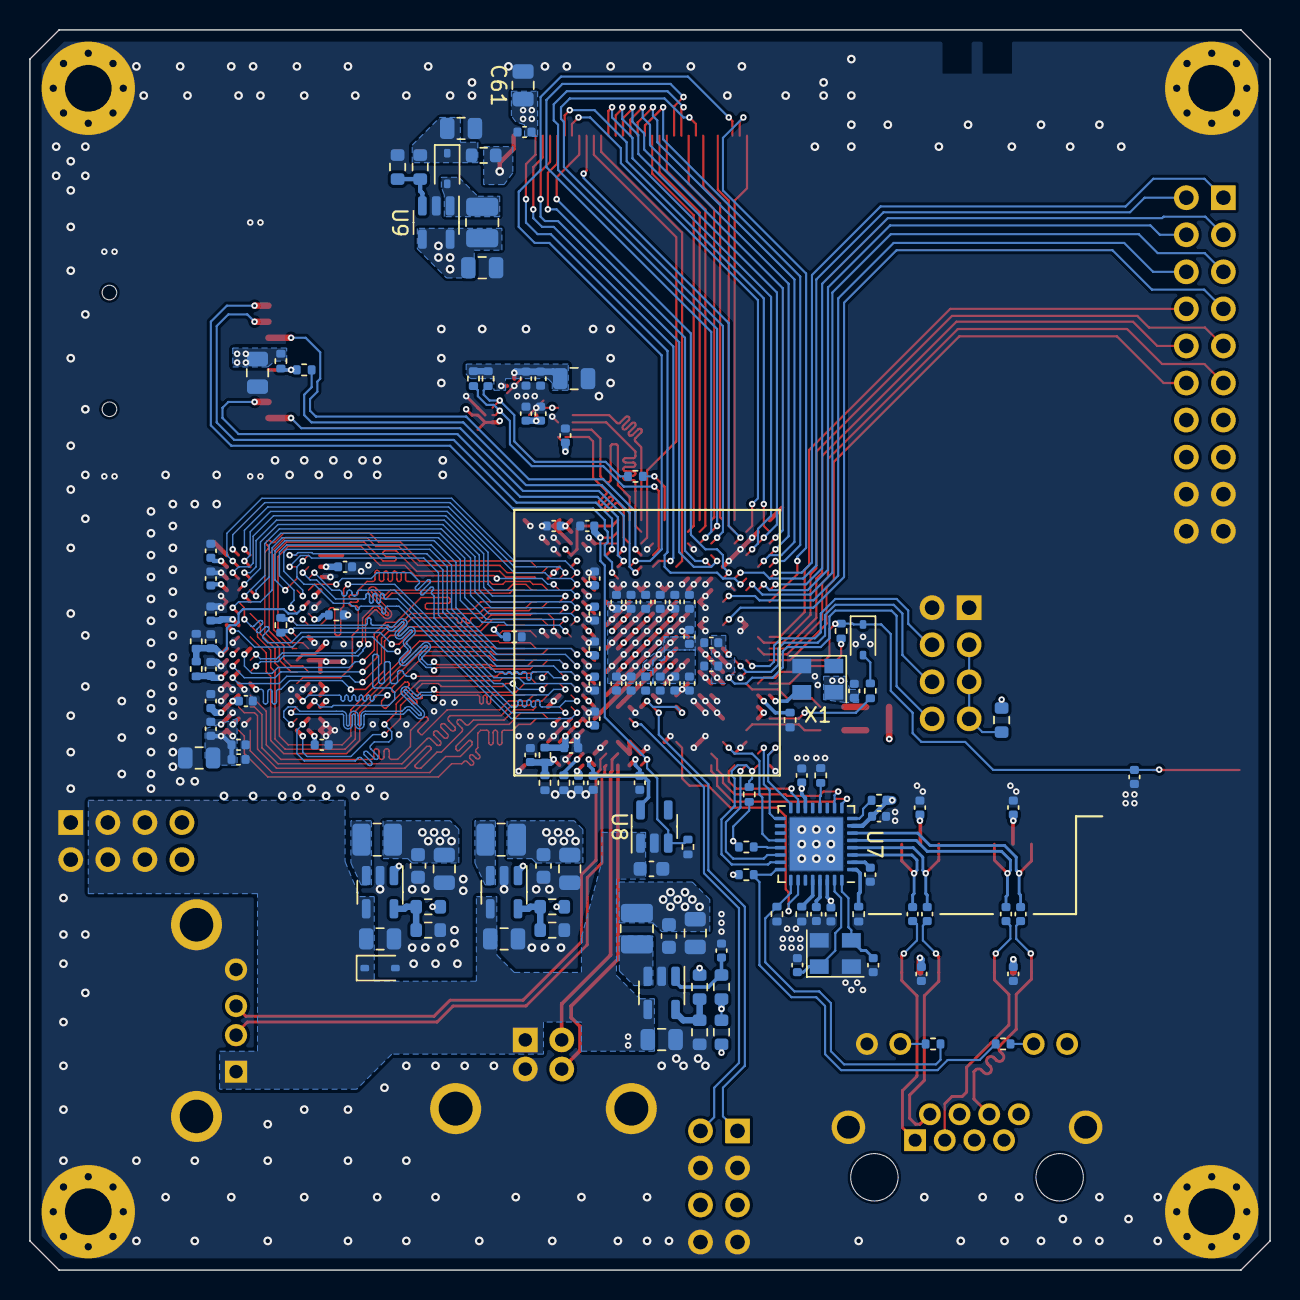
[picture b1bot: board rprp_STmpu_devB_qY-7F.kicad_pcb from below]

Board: 4 copper layers, 85.0 x 85.0 mm, 164 parts (133 on the bottom side), 184 nets.

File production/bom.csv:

Designator,Footprint,Quantity,Value,LCSC Part #
"C1, C18, C20, C23, C3, C41, C49, C61, C62, C68, C7, C79",0805,12,22uF,
"C10, C11, C12, C13, C14, C15, C16, C17, C21, C22, C24, C25, C26, C28, C29, C30, C31, C32, C33, C34, C35, C36, C37, C38, C39, C4, C40, C42, C43, C44, C45, C47, C48, C50, C52, C53, C54, C55, C57, C58, C59, C6, C60, C65, C66, C67, C69, C70, C75, C76, C77, C78",0402,52,1uF,
"C19, C2, C8, C9",0603,4,1uF,
"C27, C46, C5, C63, C64, C71, C72, C73, C74",0402,9,10nF,
"C51, C56",0402,2,10pF,
"D1, D3, D8",D_SOD-323,3,1N5819WS,
"D2, D4",0603,2,LIGHT BLUE,
D5,0603,1,RED,
"FID1, FID2, FID3, FID4",Fiducial_0.5mm_Mask1.5mm,4,Fiducial,
"H1, H2, H3, H4",MountingHole_3.2mm_M3_Pad_Via,4,M3,
J1,USB_B_OST_USB-B1HSxx_Horizontal,1,USB_B,
J10,Yu-MicroSD-TF-01A,1,Micro_SD_Card_Det2,
J2,USB_A_CONNFLY_DS1095-WNR0,1,USB_A,
"J4, J7, J8",PinHeader_2x04_P2.54mm_Vertical,3,Conn_02x04_Odd_Even,
J5,PinHeader_2x10_P2.54mm_Vertical,1,Conn_02x10_Odd_Even,
J6,Hirose_FH12-40S-0.5SH_1x40-1MP_P0.50mm_Horizontal,1,Conn_01x40_MountingPin,
J9,RJ45_Amphenol_RJHSE538X,1,RJ45_LED_Shielded,
"L1, L2, L3, L5",1008,4,2.2uH,
"R1, R30",0402,2,10,
"R10, R8",0603,2,8.2k,
"R11, R17, R31, R33, R34, R35, R36, R41, R5",0402,9,10k,
R12,0402,1,0,
"R13, R14, R15, R7, R9",0603,5,10k,
R16,0603,1,2.2k,
"R18, R39, R40",0402,3,100,
"R19, R20, R22, R23, R24",0402,5,1k,
"R2, R4",0402,2,240,
"R21, R28, R3, R6",0603,4,5.1k,
R25,0402,1,3k,
"R26, R37, R38",0402,3,5.1k,
R27,0603,1,100k,
R29,0603,1,100,
R32,0402,1,2.49k,
SW1,SW_Push_1P1T_XKB_TS-1187A,1,SW_SPST,
SYM1,ESD-Logo_8.9x8mm_SilkScreen,1,SYM_ESD_Small,
"TP2, TP3, TP4",TestPoint_Pad_D1.0mm,3,T,
TR1,Transformer_Ethernet_Bourns_PT61017PEL,1,PT61017PEL,
U1,BGA-96_9.0x13.0mm_Layout2x3x16_P0.8mm,1,NT5CB256M16ER-FL,
U14,MICRON_EMMC_153,1,EMMC04G-S100-B08U,
"U2, U4, U6",TSOT-23-5,3,SY8089A,
U5,ST_LFBGA-448_18x18mm_Layout22x22_P0.8mm,1,STM32MP157FAAx,
U7,QFN-32-1EP_5x5mm_P0.5mm_EP3.65x3.65mm,1,RTL8201F,
U8,SOT-23-5,1,LP5907MFX-3.3,
U9,SOT-23-5,1,MT3540,
X1,Crystal_SMD_EuroQuartz_MT-4Pin_3.2x2.5mm,1,25MHz,
Y1,Crystal_SMD_EuroQuartz_MT-4Pin_3.2x2.5mm,1,X322525MOB4SI,
